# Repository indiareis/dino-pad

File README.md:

# dino-pad
A hackpad for a hackclub event named highway

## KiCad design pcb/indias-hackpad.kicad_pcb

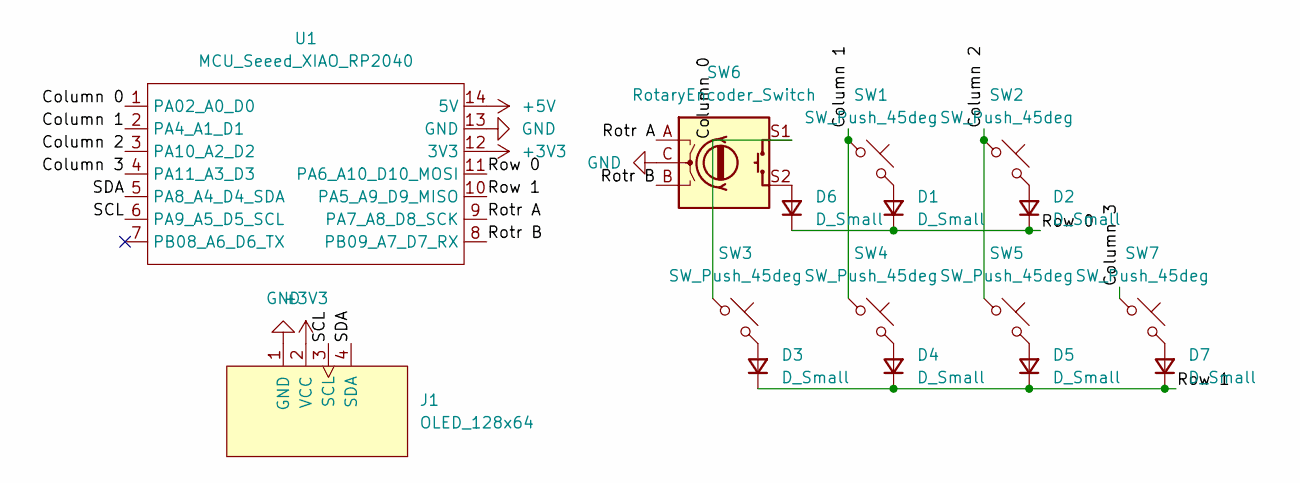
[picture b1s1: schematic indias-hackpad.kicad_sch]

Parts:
D1, D2, D3, D4, D5, D6, D7: D_Small; Diode_DO-35
J1: OLED_128x64
SW1, SW2, SW3, SW4, SW5, SW7: SW_Push_45deg; MX_PCB_1.00u
SW6: RotaryEncoder_Switch; Encoder_EC11_MX
U1: MCU_Seeed_XIAO_RP2040; Seeed_XIAO_RP2040

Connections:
+3V3: J1.2 (VCC), U1.12 (3V3)
+5V: U1.14 (5V)
/Column 0: SW3.1, SW6.S1, U1.1 (PA02_A0_D0)
/Column 1: SW1.1, SW4.1, U1.2 (PA4_A1_D1)
/Column 2: SW2.1, SW5.1, U1.3 (PA10_A2_D2)
/Column 3: SW7.1, U1.4 (PA11_A3_D3)
/Rotr A: SW6.A, U1.9 (PA7_A8_D8_SCK)
/Rotr B: SW6.B, U1.8 (PB09_A7_D7_RX)
/Row 0: D1.1 (K), D2.1 (K), D6.1 (K), U1.11 (PA6_A10_D10_MOSI)
/Row 1: D3.1 (K), D4.1 (K), D5.1 (K), D7.1 (K), U1.10 (PA5_A9_D9_MISO)
/SCL: J1.3 (SCL), U1.6 (PA9_A5_D5_SCL)
/SDA: J1.4 (SDA), U1.5 (PA8_A4_D4_SDA)
GND: J1.1 (GND), SW6.C, U1.13 (GND)
unnamed: D1.2 (A), SW1.2
unnamed: D2.2 (A), SW2.2
unnamed: D3.2 (A), SW3.2
unnamed: D4.2 (A), SW4.2
unnamed: D5.2 (A), SW5.2
unnamed: D6.2 (A), SW6.S2
unnamed: D7.2 (A), SW7.2

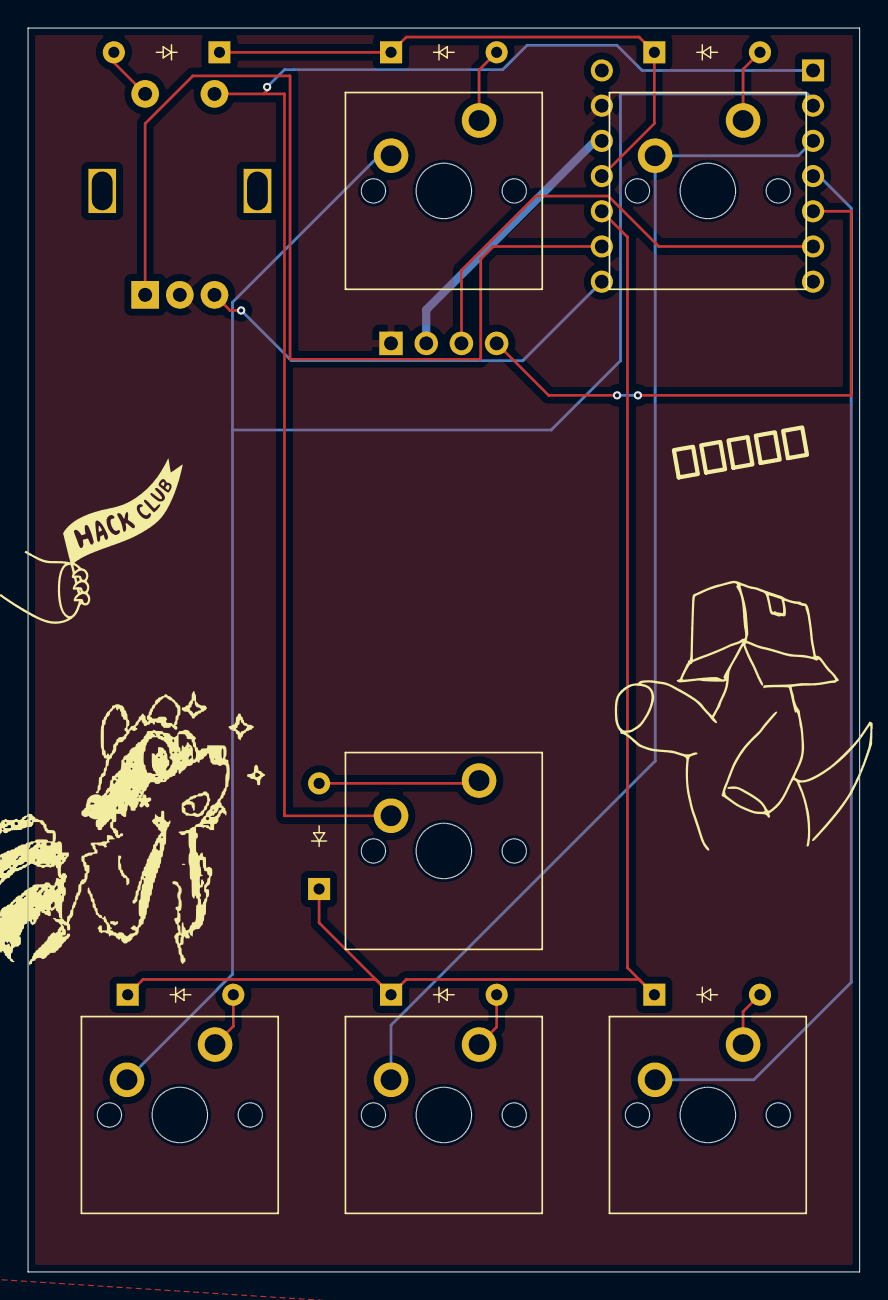
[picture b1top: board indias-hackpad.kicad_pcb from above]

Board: 2 copper layers, 60.0 x 89.8 mm, 16 parts (1 on the bottom side), 19 nets.

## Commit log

2025-06-12 U dumasss it should be india commiting < India is here
